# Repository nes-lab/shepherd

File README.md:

# SHEpHERD: SyncHronized Energy Harvesting Emulator RecorDer

**Testbed-Website**: <https://nes-lab.github.io/shepherd-nova>

**Python-Tools for Users**: <https://github.com/nes-lab/shepherd-tools>

**Documentation**: <https://nes-lab.github.io/shepherd>

**Main Project**: <https://github.com/nes-lab/shepherd>

**Targets-HW & -SW**: <https://github.com/nes-lab/shepherd-targets>

**WebAPI-Repo**: <https://github.com/nes-lab/shepherd-webapi>

**Dev-Documentation**: <https://github.com/orgua/shepherd-v2-planning>

---

Batteryless sensor nodes depend on harvesting energy from their environment.
Developing solutions involving groups of batteryless nodes requires a tool to analyze, understand and replicate spatio-temporal harvesting conditions.
*shepherd* is a testbed for the batteryless Internet of Things, allowing to record harvesting conditions at multiple points in space over time.
The recorded data can be replayed to attached wireless sensor nodes, examining their behavior under the constraints of spatio-temporal energy availability.

**Features**

- High-speed, high resolution current and voltage sensing
- Technology-agnostic: Currently, solar and kinetic energy harvesting are supported
- Remote programming/debugging of ARM Cortex-M MCUs using Serial-Wire-Debug
- High resolution, synchronized GPIO tracing
- Configurable, constant voltage power supply for attached sensor nodes
- Level-translated serial connection to the attached sensor nodes

For a detailed description see our [Paper](https://wwwpub.zih.tu-dresden.de/~mzimmerl/pubs/geissdoerfer19shepherd.pdf) or the [official documentation](https://nes-lab.github.io/shepherd/).

A *shepherd* instance consists of a group of spatially distributed *shepherd* nodes that are time-synchronized with each other.
Each *shepherd* node consists of a [BeagleBone](https://beagleboard.org/bone), the *shepherd* cape and either an energy harvesting source or a target MCU board to test.

This repository contains the hardware design files for the shepherd cape, the software running on each *shepherd* node as well as the tool to orchestrate a group of *shepherd* nodes connected to a network.

## Quickstart

Start by assembling your *shepherd* nodes, consisting of a BeagleBone Green/Black, a *shepherd* cape, a harvesting capelet and a target capelet.
The next step is to manually install the latest Ubuntu Linux on each BeagleBone.
You can install it to SD-card or the on-board eMMC flash, following [the official instructions](https://elinux.org/BeagleBoardUbuntu).
Make sure to follow the instructions for **BeagleBone**. Alternatively there are two more detailed guides in the [shepherd documentation](https://nes-lab.github.io/shepherd/user/getting_started.html).

The following instructions describe how to install the *shepherd* software on a group of *shepherd* nodes connected to an Ethernet network.
We assume that your local machine is connected to the same network, that the nodes have internet access and that you know the IP address of each node.

If you haven't done it yet, clone this repository to your local machine:

```shell
git clone https://github.com/nes-lab/shepherd.git
```

Next, install the tools used for installing and controlling the *shepherd* nodes.
We'll use [Ansible](https://www.ansible.com/) to remotely roll out the basic configuration to each *shepherd* node and *shepherd-herd* to orchestrate recording/emulation across all nodes.
The tools are hosted on `PyPI` and require Python version >= 3.6.
You'll also need to have `sshpass` installed on your machine, which is available through the package management system of all major distributions.
Install the tools using `pip`:

```shell
pip3 install ansible shepherd-herd
```

The `inventory/herd.yaml` file shows an example of how to provide the host names and known IP addresses of your BeagleBones.
Adjust it to reflect your setup.
You can arbitrarily choose and assign the hostnames (sheep0, sheep1, in this example) and the ansible_user (jane in this example).
[**TODO:** update description with roles].

```yaml
sheep:
  hosts:
    sheep0:
        ansible_host: 192.168.1.100
    sheep1:
        ansible_host: 192.168.1.101
    sheep2:
        ansible_host: 192.168.1.102
  vars:
    ansible_user: jane
```

Now run the `bootstrap.yml` *Ansible* playbook, which sets the hostname, creates a user and enables passwordless ssh and sudo:

```shell
ansible-playbook deploy/bootstrap.yml
```

Finally, use the `deploy.yml` playbook to set up the *shepherd* software with the configured roles from inventory:

```shell
ansible-playbook deploy/deploy.yml
```

## Usage

Record two minutes of data:

```shell
shepherd-herd harvester -d 120 -o recording.h5 -a mppt_voc
```

The command starts the recording asynchronously and returns after all nodes have started recording.
While the nodes are still recording (indicated by blinking of LED 1 and 2), prepare a directory on your local machine:

```shell
mkdir ~/shepherd_recordings
```

After the nodes stop blinking, you can retrieve the data to analyze it on your local machine:

```shell
shepherd-herd retrieve recording.h5 ~/shepherd_recordings
```

For a detailed description of the [HDF5](https://en.wikipedia.org/wiki/Hierarchical_Data_Format) based data format, refer to the [corresponding documentation](https://shepherd-testbed.readthedocs.io/en/latest/user/data_format.html).

Finally, replay the previously recorded data to the attached sensor nodes, recording their power consumption:

```shell
shepherd-herd emulator -o consumption.h5 recording.h5
```

Try `shepherd-herd --help` or check out the documentation [here](https://shepherd-testbed.readthedocs.io/en/latest/user/cli.html#shepherd-herd) for a list of all options.

## Problems and Questions

If you experience issues or require additional features, please get in touch via e-mail or by creating an issue on GitHub. The issue-tab also gives an overview for current roadmaps and milestones.

## People

*shepherd* development is lead at the Networked Embedded Systems Lab at TU Dresden & TU Darmstadt as part of the DFG-funded project Next-IoT.

The following people have contributed to *shepherd*:

- [Kai Geissdoerfer](https://www.researchgate.net/profile/Kai_Geissdoerfer)
- [Mikolaj Chwalisz](https://www.tkn.tu-berlin.de/team/chwalisz/)
- [Marco Zimmerling](https://wwwpub.zih.tu-dresden.de/~mzimmerl/)
- [Justus Paulick](https://github.com/kugelbit)
- [Boris Blokland](https://github.com/borro0)
- [Jonas Kubicki](https://github.com/jonkub)
- [Ingmar Splitt](https://github.com/nes-lab)

## Release-Procedure

Once you have a clean, stable and tested version, you should bump the version number to current year, month and release-number (YYYY.MM.r).

- increase version number by executing ``bump2version`` (see cmds below)
- update changelog in ``CHANGELOG.md``
- run unittests locally
  - sheep-package on observers
  - herd-tool on host
  - pru-python-module (in `software/firmware/pru0-module-py`)
  - fresh installation on Linux image via ansible
  - additionally every push gets automatically tested by GitHub workflows
- install and run ``prek`` for QA-Checks (pre-commit plugin-replacement), see steps below
- move code from dev-branch to main by PR
- add tag to commit - reflecting current version number - i.e. ``v25.5.1``
  - GitHub automatically creates a release & pushes the release to PyPI
- update release-text with latest Changelog (from `CHANGELOG.md`)
- rebase dev-branch

```Shell
prek run --all-files

# additional QA-Tests (currently with open issues)
ty check

bump2version --allow-dirty --new-version 2026.11.1 patch
# version-format: YYYY.MM.r
```

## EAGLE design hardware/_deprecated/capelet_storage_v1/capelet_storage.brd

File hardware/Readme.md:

# Shepherd specific Hardware

## Overview

Hardware-Subdirectories contain the necessary design-files to manufacture a shepherd observer node.

- `_deprecated`: design files for hardware that still floats around in the lab
- `cape_v#.#`: most recent version of shepherd cape for the BBone
- `case_lasercut`: deployment version for testbed
- ~~`power_in`:~~ low noise voltage regulator with < 17 V Input for TP-Link POE-Adapters that fail to produce 5V on newer Cisco Switches
- Targets are in dedicated [targets-repo](https://github.com/nes-lab/shepherd-targets/tree/main/hardware)

## Photos

### Cape v2.4

More pictures are stored for QA in [planning-repo](https://github.com/orgua/shepherd-v2-planning/tree/main/doc_testbed/photos_PCBs).

### Cape v2.5

No pictures available yet. Hardware is currently tested and then deployed.

### Observers

Assembled in October 2024 for the deployment at TU Dresden. These nodes contain:

- TP-Link POE Splitter
- BeagleBone Green
- Shepherd Cape v2.4
- [nRF FRAM Target v1.3](https://github.com/nes-lab/shepherd-targets/tree/main/hardware/shepherd_nRF_FRAM_Target_v1.3e)
- Power-in-PCB
- Laser-cut case

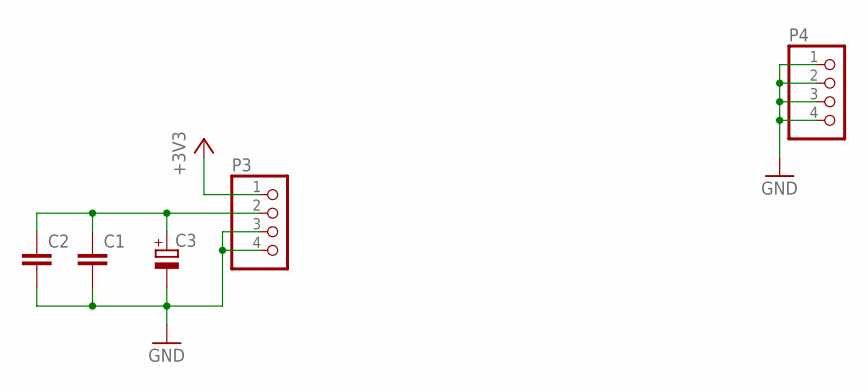
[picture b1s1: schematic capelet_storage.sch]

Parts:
C1: C_SMD0805; CAPC2012X145
C2: C_SMD1210; CAPC3225X280
C3: CPOL-EUE5-8.5; E5-8,5
P3, P4: PINHD-1X4; 1X04

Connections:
+3V3: P3.1
GND: C1.2, C2.2, C3.-, P3.3, P3.4, P4.1, P4.2, P4.3, P4.4
unnamed: C1.1, C2.1, C3.+, P3.2

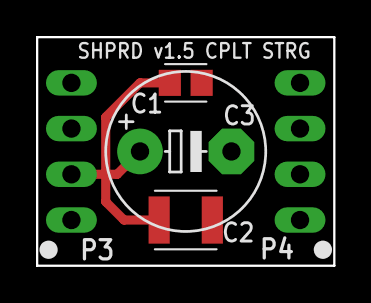
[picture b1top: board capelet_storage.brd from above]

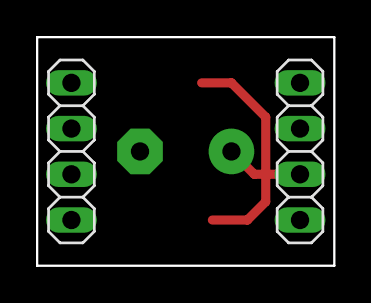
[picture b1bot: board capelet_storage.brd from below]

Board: 2 copper layers, 16.5 x 12.7 mm, 6 parts (2 on the bottom side), 2 nets.

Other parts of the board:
U$1: SHPRD_CPLT_S

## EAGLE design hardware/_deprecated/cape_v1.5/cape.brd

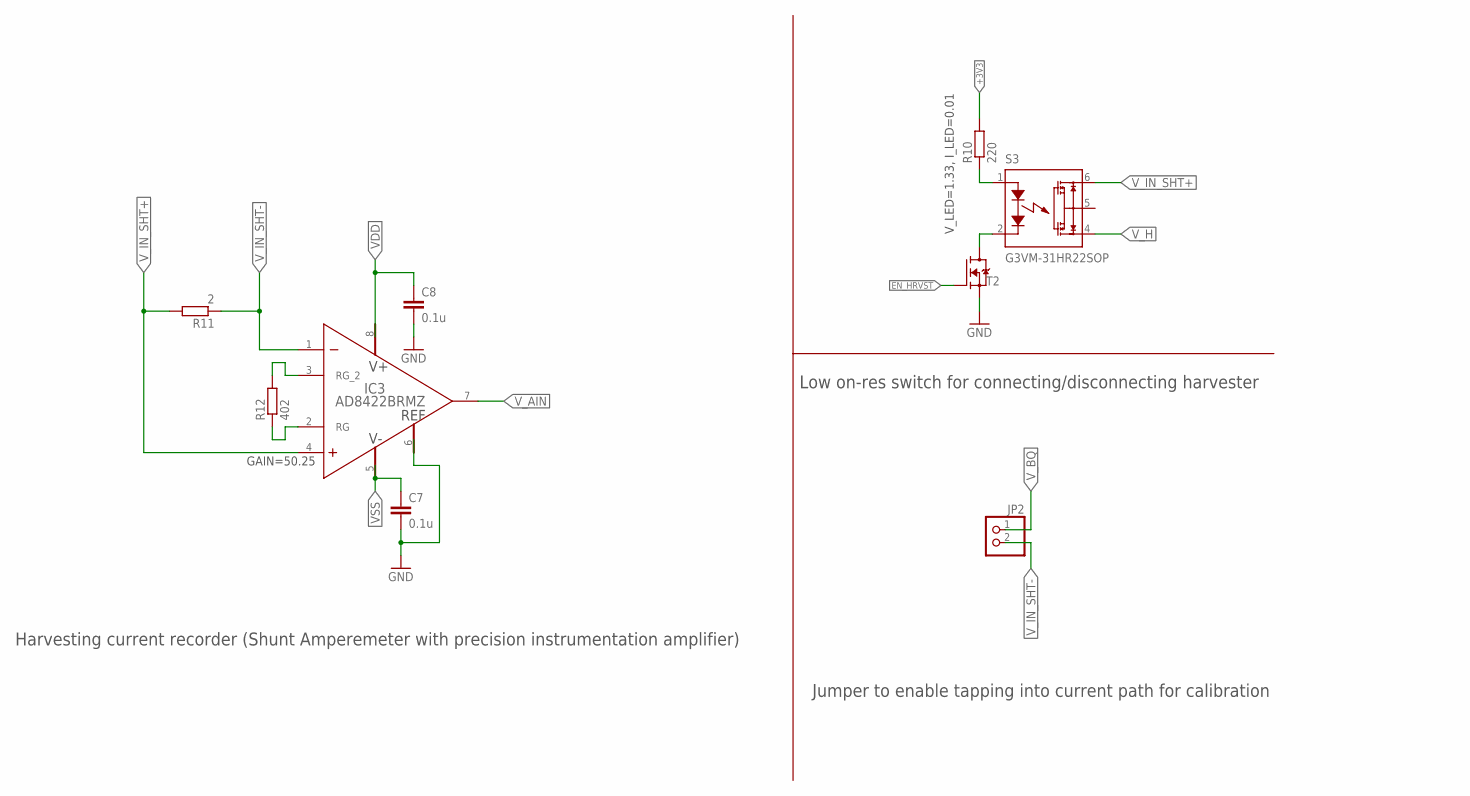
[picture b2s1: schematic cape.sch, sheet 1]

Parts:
C7, C8: 0.1u; CAPC1005X55
IC3: AD8422BRMZ; RM_8-L
JP2: PINHD-1X2; 1X02
R10: 220; RESC1608X55
R11: 2; RESC1608X55
R12: 402; RESC1608X55
S3: G3VM-31HR22SOP; SOP06
T2: SI2374DSSOT23-VSHAY; SOT95P237X112-3

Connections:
+3V3: R10.2; also elsewhere on the board
EN_HRVST: T2.1 (G); also elsewhere on the board
GND: C7.2, C8.2, IC3.6 (REF), T2.2 (S); also elsewhere on the board
unnamed: R10.1, S3.1 (A)
unnamed: IC3.3 (RG_2), R12.2
unnamed: IC3.2 (RG), R12.1
unnamed: S3.2 (K), T2.3 (D)
VDD: C8.1, IC3.8 (V+); also elsewhere on the board
VSS: C7.1, IC3.5 (V-); also elsewhere on the board
V_AIN: IC3.7 (OUT); also elsewhere on the board
V_BQ: JP2.1; also elsewhere on the board
V_H: S3.4 (D2); also elsewhere on the board
V_IN_SHT+: IC3.4 (IN+), R11.2, S3.6 (D1); also elsewhere on the board
V_IN_SHT-: IC3.1 (IN-), JP2.2, R11.1; also elsewhere on the board

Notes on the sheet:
V_LED=1.33, I_LED=0.01
GAIN=50.25
Harvesting current recorder (Shunt Amperemeter with precision instrumentation amplifier)
Low on-res switch for connecting/disconnecting harvester
Jumper to enable tapping into current path for calibration

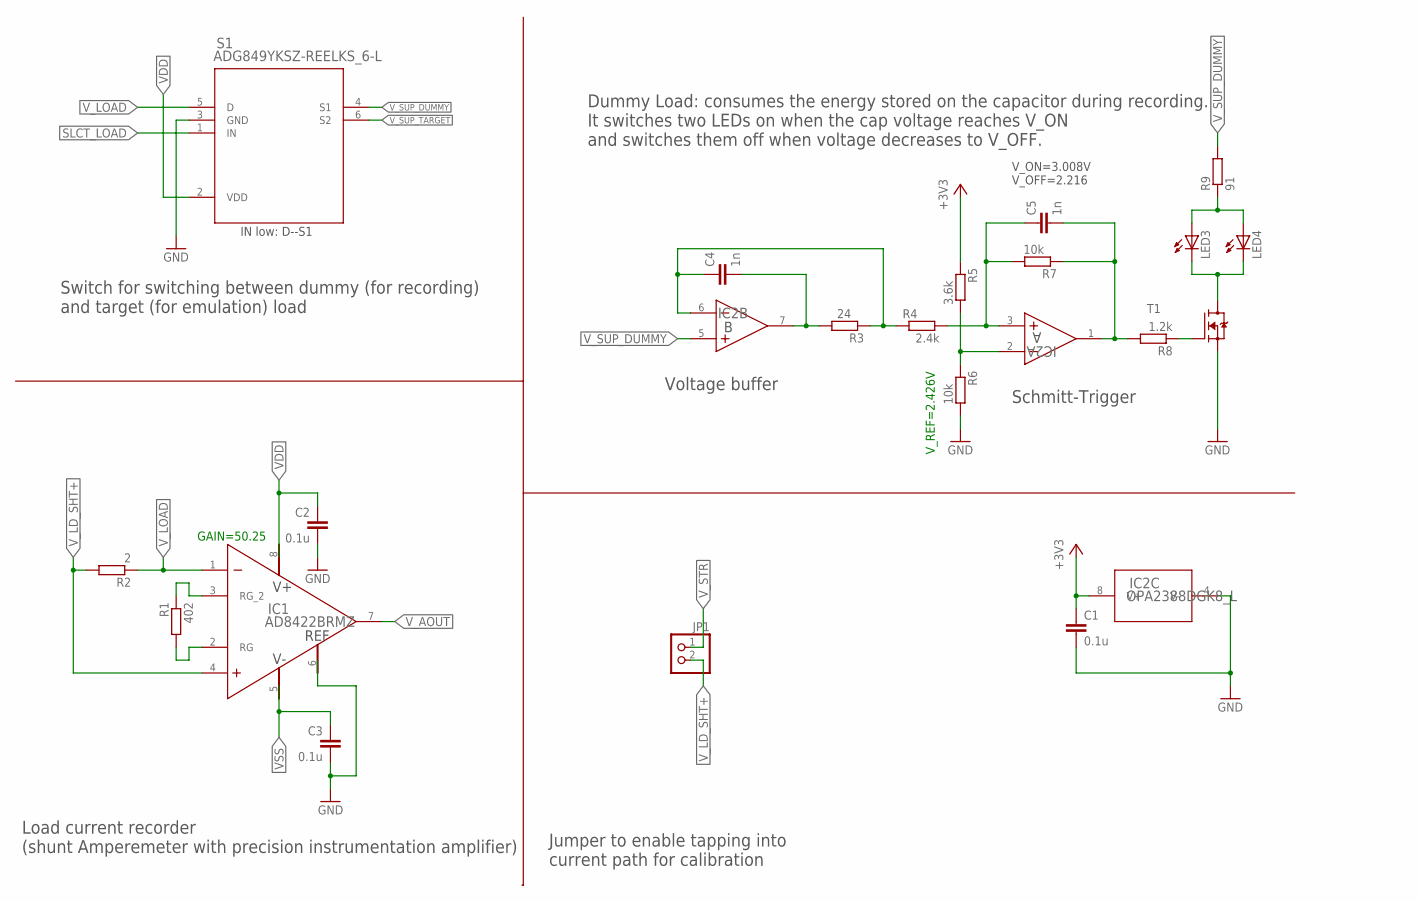
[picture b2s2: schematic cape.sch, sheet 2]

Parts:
C1, C2, C3: 0.1u; CAPC1005X55
C4, C5: 1n; CAPC1005X55
IC1: AD8422BRMZ; RM_8-L
IC2: OPA2388DGK8_L; DGK8-L
JP1: PINHD-1X2; 1X02
LED3, LED4: 598-8130-107FLED_0805; LEDC2012X75
R1: 402; RESC1608X55
R2: 2; RESC1608X55
R3: 24; RESC1005X40
R4: 2.4k; RESC1005X40
R5: 3.6k; RESC1005X40
R6, R7: 10k; RESC1005X40
R8: 1.2k; RESC1005X40
R9: 91; RESC1608X55
S1: ADG849YKSZ-REELKS_6-L; KS_6-L
T1: SI2374DSSOT23-VSHAY; SOT95P237X112-3

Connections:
+3V3: C1.1, IC2.8 (V+), R5.1; also elsewhere on the board
GND: C1.2, C2.2, C3.2, IC1.6 (REF), IC2.4 (V-), R6.2, S1.3 (GND), T1.2 (S); also elsewhere on the board
unnamed: R8.1, T1.1 (G)
unnamed: LED3.2 (A), LED4.2 (A), R9.1
unnamed: C5.2, IC2.1 (OUT), R7.1, R8.2
unnamed: LED3.1 (C), LED4.1 (C), T1.3 (D)
unnamed: C5.1, IC2.3 (IN+), R4.2, R7.2
unnamed: IC2.2 (IN-), R5.2, R6.1
unnamed: C4.1, IC2.6 (IN-), R3.1, R4.1
unnamed: C4.2, IC2.7 (OUT), R3.2
unnamed: IC1.2 (RG), R1.2
unnamed: IC1.3 (RG_2), R1.1
SLCT_LOAD: S1.1 (IN); also elsewhere on the board
VDD: C2.1, IC1.8 (V+), S1.2 (VDD); also elsewhere on the board
VSS: C3.1, IC1.5 (V-); also elsewhere on the board
V_AOUT: IC1.7 (OUT); also elsewhere on the board
V_LD_SHT+: IC1.4 (IN+), JP1.2, R2.2; also elsewhere on the board
V_LOAD: IC1.1 (IN-), R2.1, S1.5 (D); also elsewhere on the board
V_STR: JP1.1; also elsewhere on the board
V_SUP_DUMMY: IC2.5 (IN+), R9.2, S1.4 (S1)
V_SUP_TARGET: S1.6 (S2); also elsewhere on the board

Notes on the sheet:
IN low: D--S1
GAIN=50.25
V_REF=2.426V
V_ON=3.008V V_OFF=2.216
Dummy Load: consumes the energy stored on the capacitor during recording. It switches two LEDs on when the cap voltage reaches V_ON and switches them off when voltage decreases to V_OFF.
Voltage buffer
Schmitt-Trigger
Switch for switching between dummy (for recording) and target (for emulation) load
Load current recorder (shunt Amperemeter with precision instrumentation amplifier)
Jumper to enable tapping into current path for calibration

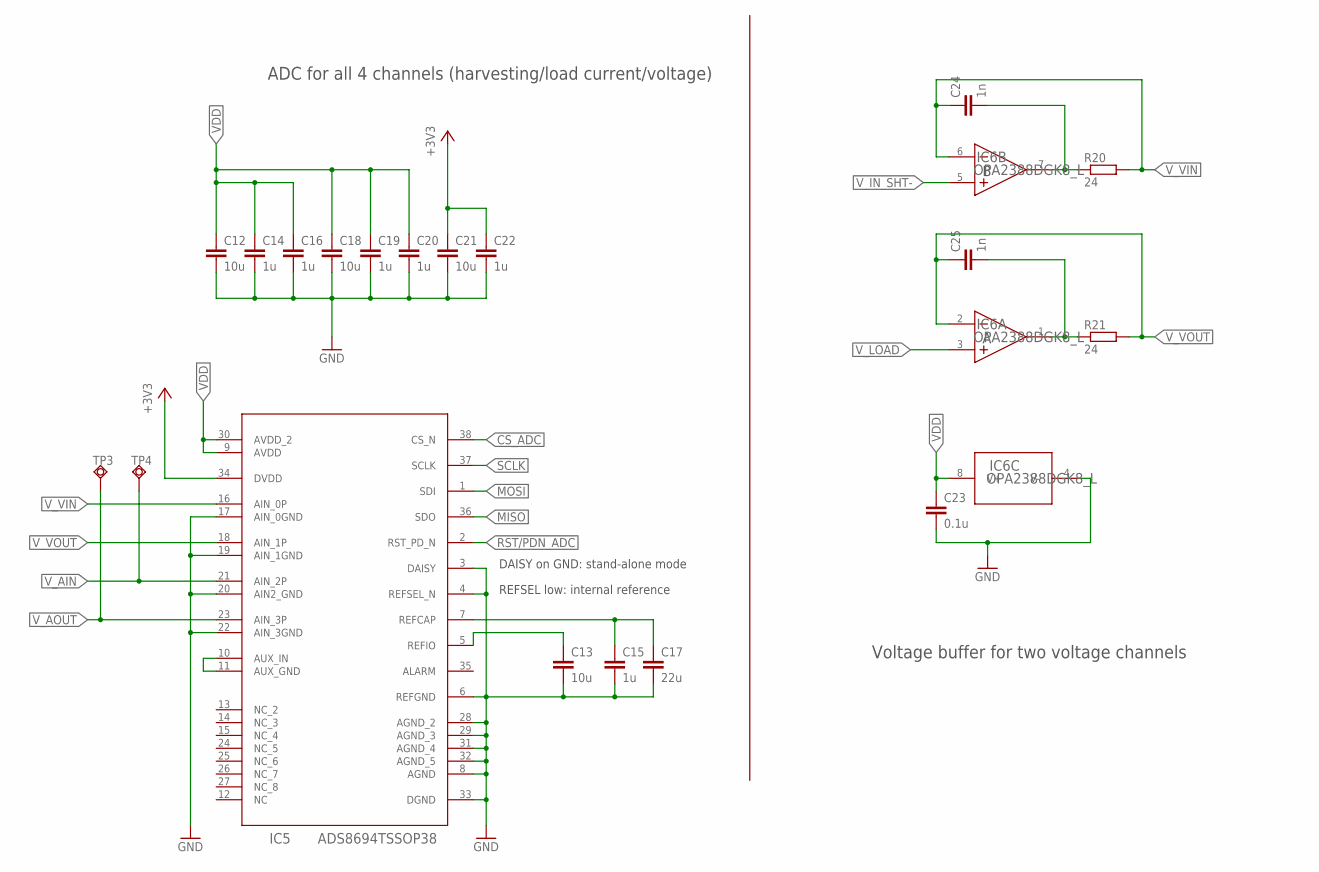
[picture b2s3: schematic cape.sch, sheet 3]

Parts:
C12, C13, C18, C21: 10u; CAPC2012X145
C14, C15, C16, C19, C20, C22: 1u; CAPC1608X95
C17: 22u; CAPC3225X280
C23: 0.1u; CAPC1005X55
C24, C25: 1n; CAPC1005X55
IC5: ADS8694TSSOP38; TSSOP38
IC6: OPA2388DGK8_L; DGK8-L
R20, R21: 24; RESC1005X40
TP3, TP4: TPSQTP06R; TP06R

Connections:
+3V3: C21.1, C22.1, IC5.34 (DVDD); also elsewhere on the board
CS_ADC: IC5.38 (CS_N); also elsewhere on the board
GND: C12.2, C13.2, C14.2, C15.2, C16.2, C17.2, C18.2, C19.2, C20.2, C21.2, C22.2, C23.2, IC5.3 (DAISY), IC5.4 (REFSEL_N), IC5.6 (REFGND), IC5.8 (AGND), IC5.17 (AIN_0GND), IC5.19 (AIN_1GND), IC5.20 (AIN2_GND), IC5.22 (AIN_3GND), IC5.28 (AGND_2), IC5.29 (AGND_3), IC5.31 (AGND_4), IC5.32 (AGND_5), IC5.33 (DGND), IC6.4 (V-); also elsewhere on the board
MISO: IC5.36 (SDO); also elsewhere on the board
MOSI: IC5.1 (SDI); also elsewhere on the board
unnamed: C13.1, IC5.5 (REFIO)
unnamed: C15.1, C17.1, IC5.7 (REFCAP)
unnamed: IC5.10 (AUX_IN), IC5.11 (AUX_GND)
unnamed: C25.2, IC6.1 (OUT), R21.1
unnamed: C24.2, IC6.7 (OUT), R20.1
RST/PDN_ADC: IC5.2 (RST_PD_N); also elsewhere on the board
SCLK: IC5.37 (SCLK); also elsewhere on the board
VDD: C12.1, C14.1, C16.1, C18.1, C19.1, C20.1, C23.1, IC5.9 (AVDD), IC5.30 (AVDD_2), IC6.8 (V+); also elsewhere on the board
V_AIN: IC5.21 (AIN_2P), TP4.TP; also elsewhere on the board
V_AOUT: IC5.23 (AIN_3P), TP3.TP; also elsewhere on the board
V_IN_SHT-: IC6.5 (IN+); also elsewhere on the board
V_LOAD: IC6.3 (IN+); also elsewhere on the board
V_VIN: C24.1, IC5.16 (AIN_0P), IC6.6 (IN-), R20.2
V_VOUT: C25.1, IC5.18 (AIN_1P), IC6.2 (IN-), R21.2

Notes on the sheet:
REFSEL low: internal reference
DAISY on GND: stand-alone mode
ADC for all 4 channels (harvesting/load current/voltage)
Voltage buffer for two voltage channels

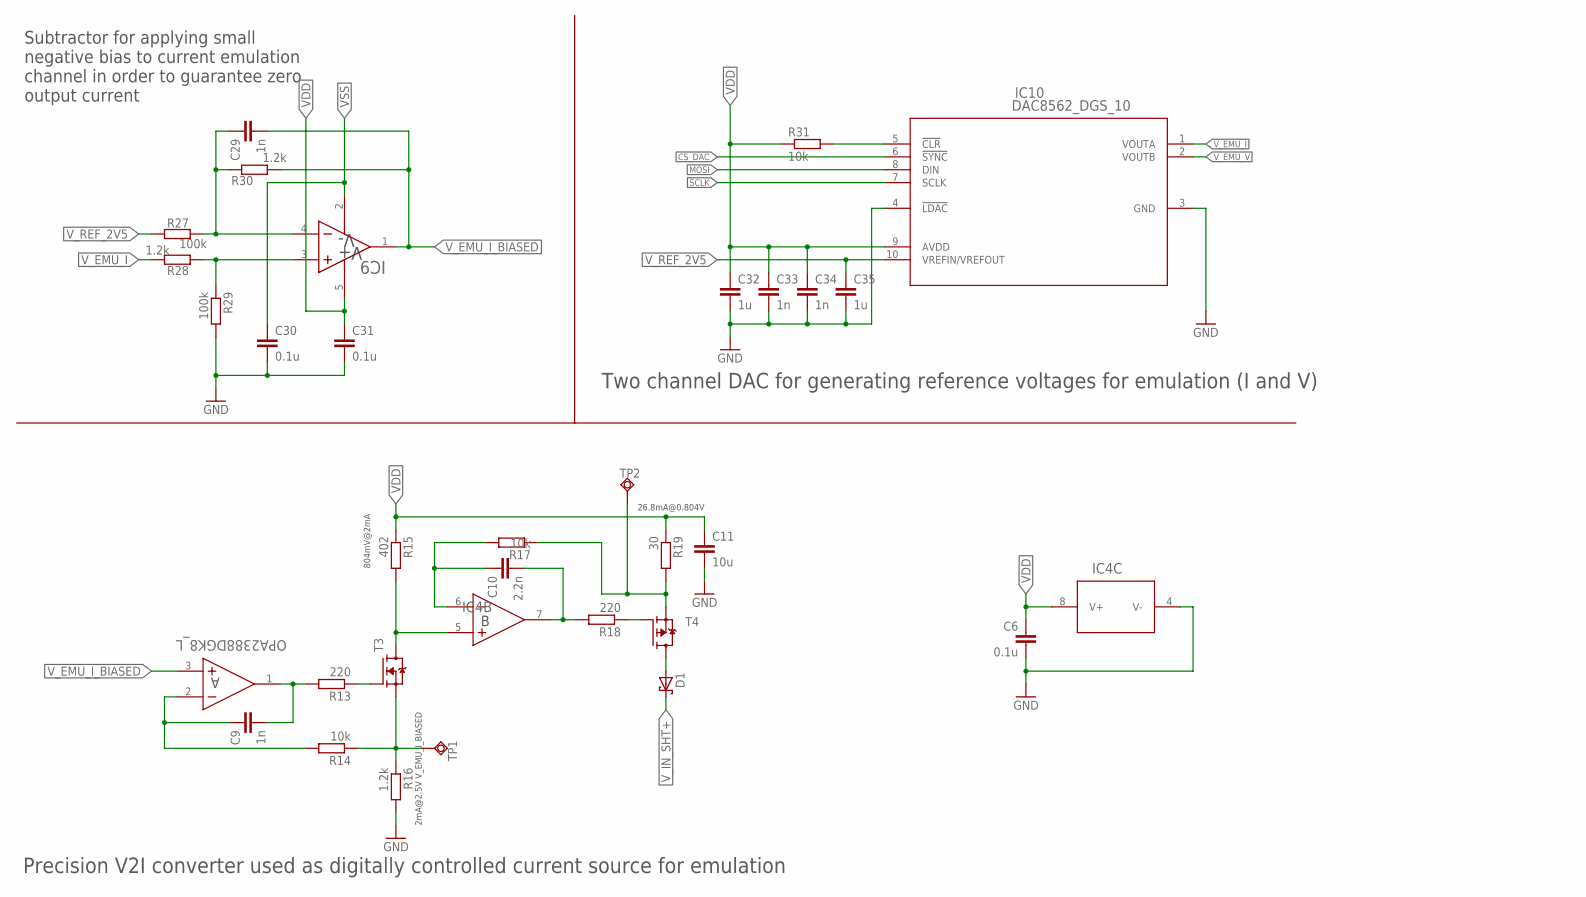
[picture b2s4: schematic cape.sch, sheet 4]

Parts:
C6, C30, C31: 0.1u; CAPC1005X55
C9, C29, C33, C34: 1n; CAPC1005X55
C10: 2.2n; CAPC1005X55
C11: 10u; CAPC2012X145
C32, C35: 1u; CAPC1608X95
D1: BAT43WS-HE3SOD-323; SOD2513X110
IC4: OPA2388DGK8_L; DGK8-L
IC9: LMP7701MF; DBV5-L
IC10: DAC8562_DGS_10; DGS10
R13, R18: 220; RESC1608X55
R14, R17, R31: 10k; RESC1005X40
R15: 402; RESC1608X55
R16, R28, R30: 1.2k; RESC1005X40
R19: 30; RESC1005X40
R27, R29: 100k; RESC1005X40
T3: SI2374DSSOT23-VSHAY; SOT95P237X112-3
T4: SI2307SOT23-VSHAY; SOT95P237X112-3
TP1, TP2: TPSQTP06R; TP06R

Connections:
CS_DAC: IC10.6 (!SYNC); also elsewhere on the board
GND: C6.2, C11.2, C30.2, C31.2, C32.2, C33.2, C34.2, C35.2, IC4.4 (V-), IC10.3 (GND), IC10.4 (!LDAC), R16.2, R29.2; also elsewhere on the board
MOSI: IC10.8 (DIN); also elsewhere on the board
unnamed: C9.2, IC4.1 (OUT), R13.2
unnamed: C9.1, IC4.2 (IN-), R14.2
unnamed: IC10.5 (!CLR), R31.2
unnamed: D1.2 (A), T4.3 (D)
unnamed: C29.1, IC9.4 (IN-), R27.1, R30.2
unnamed: IC9.3 (IN+), R28.1, R29.1
unnamed: R13.1, T3.1 (G)
unnamed: R14.1, R16.1, T3.2 (S), TP1.TP
unnamed: IC4.5 (IN+), R15.2, T3.3 (D)
unnamed: C10.1, IC4.6 (IN-), R17.2
unnamed: C10.2, IC4.7 (OUT), R18.2
unnamed: R18.1, T4.1 (G)
unnamed: R17.1, R19.2, T4.2 (S), TP2.TP
SCLK: IC10.7 (SCLK); also elsewhere on the board
VDD: C6.1, C11.1, C31.1, C32.1, C33.1, C34.1, IC4.8 (V+), IC9.5 (V+), IC10.9 (AVDD), R15.1, R19.1, R31.1; also elsewhere on the board
VSS: C30.1, IC9.2 (V-); also elsewhere on the board
V_EMU_I: IC10.1 (VOUTA), R28.2
V_EMU_I_BIASED: C29.2, IC4.3 (IN+), IC9.1 (OUT), R30.1
V_EMU_V: IC10.2 (VOUTB); also elsewhere on the board
V_IN_SHT+: D1.1 (C); also elsewhere on the board
V_REF_2V5: C35.1, IC10.10 (VREFIN/VREFOUT), R27.2

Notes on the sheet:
Two channel DAC for generating reference voltages for emulation (I and V)
Subtractor for applying small negative bias to current emulation channel in order to guarantee zero output current
2mA@2.5V V_EMU_I_BIASED
804mV@2mA
26.8mA@0.804V
Precision V2I converter used as digitally controlled current source for emulation

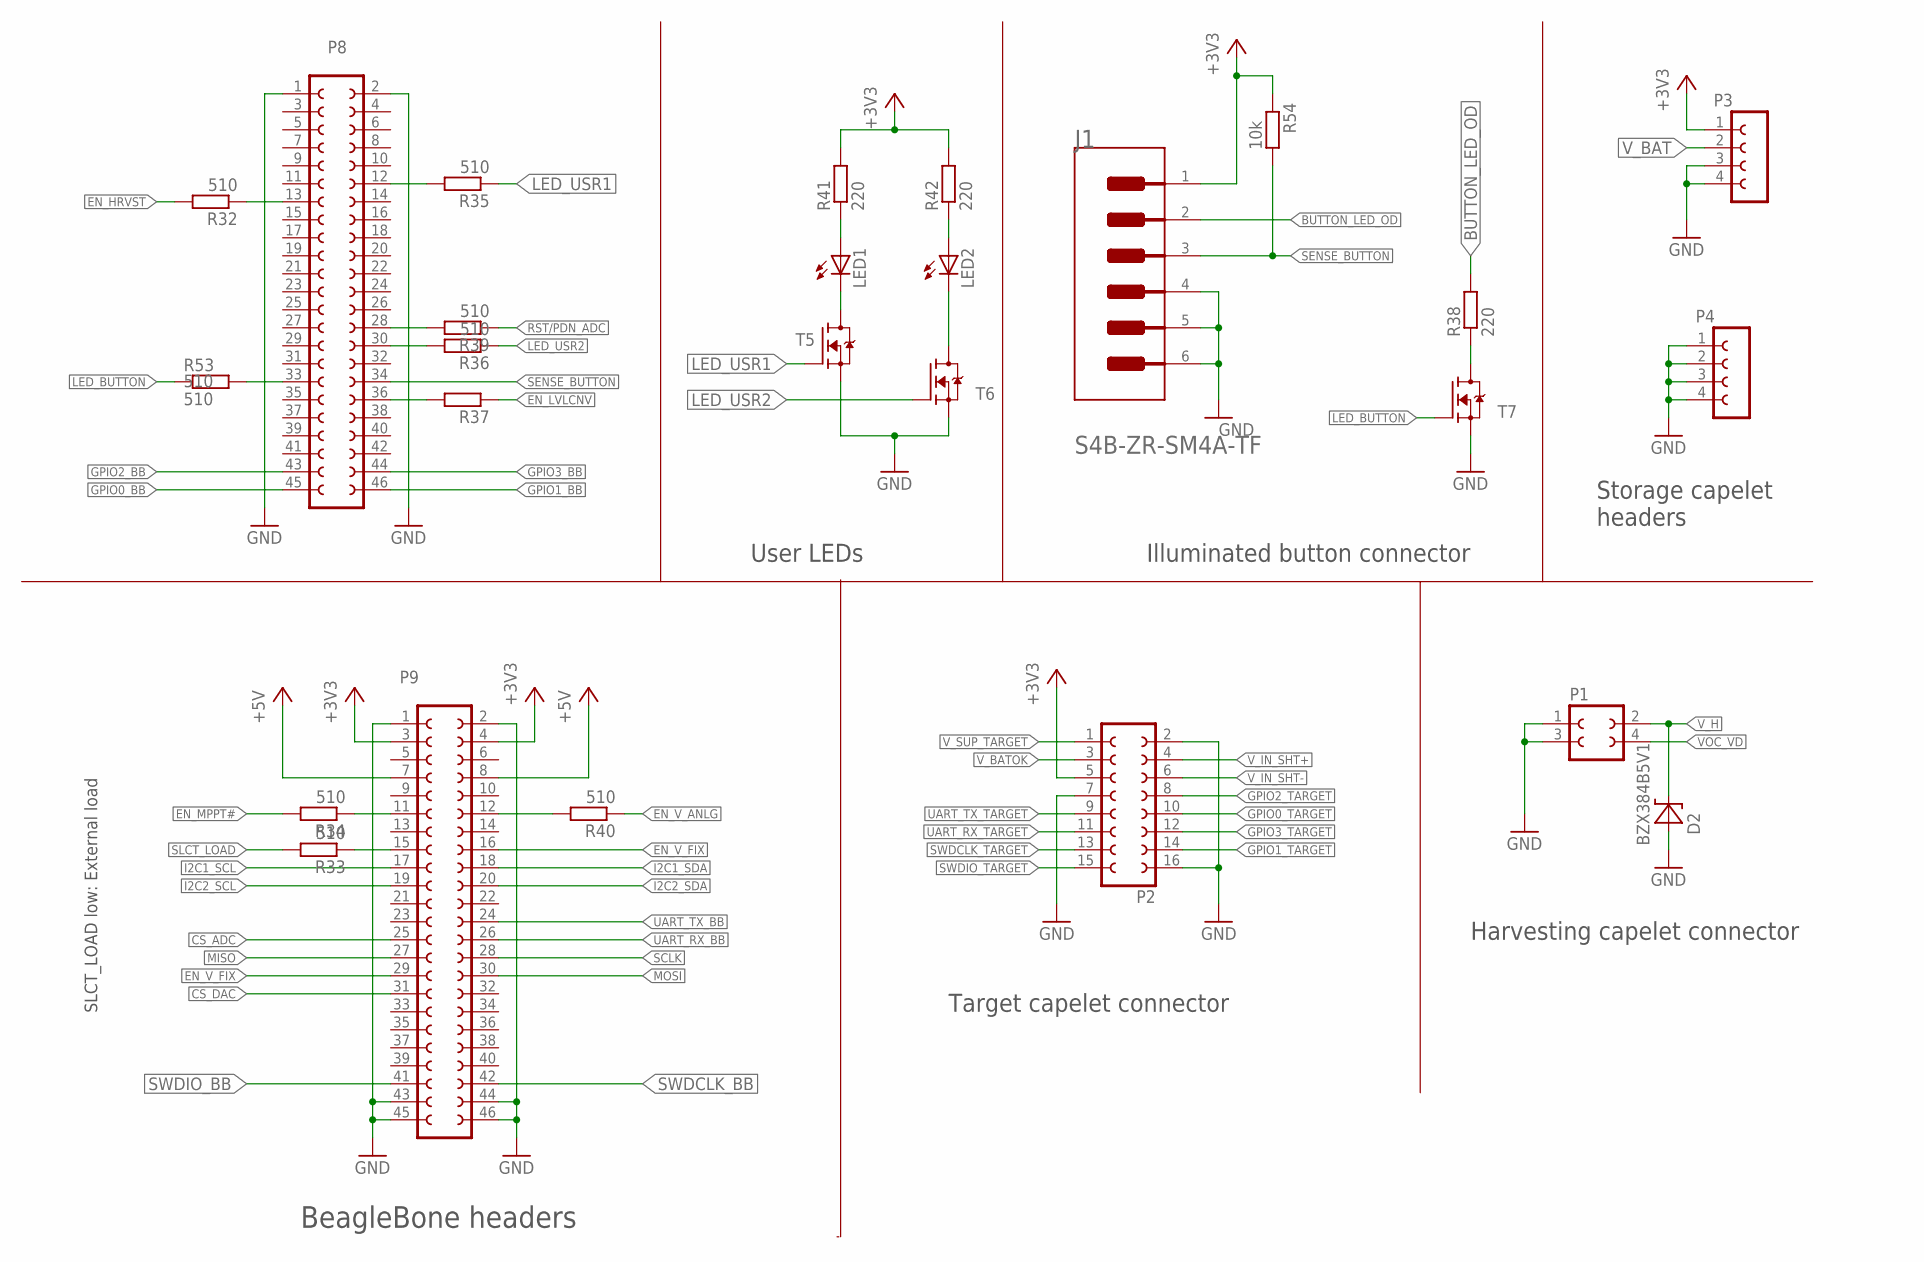
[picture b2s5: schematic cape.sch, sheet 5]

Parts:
D2: BZX384B5V1; SOD2513X110
J1: JST_S4B-ZR-SM4A-TFJST_S4B-ZR-SM4A-TF_0_0; JST_S4B-ZR-SM4A-TF_0
LED1, LED2: 598-8130-107FLED_0805; LEDC2012X75
P1: FE02-2
P2: FE08-2
P3, P4: FE04-1
P8, P9: FE23-2
R32, R33, R34, R35, R36, R37, R39, R40, R53: 510; RESC1005X40
R38, R41, R42: 220; RESC1608X55
R54: 10k; RESC1005X40
T5, T6, T7: SI2374DSSOT23-VSHAY; SOT95P237X112-3

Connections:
+3V3: J1.1, P2.5, P3.1, P9.3, P9.4, R41.2, R42.2, R54.1; also elsewhere on the board
+5V: P9.7, P9.8; also elsewhere on the board
BUTTON_LED_OD: J1.2, R38.2
CS_ADC: P9.25; also elsewhere on the board
CS_DAC: P9.31; also elsewhere on the board
EN_HRVST: R32.2; also elsewhere on the board
EN_LVLCNV: R37.1; also elsewhere on the board
EN_MPPT#: R34.2; also elsewhere on the board
EN_V_ANLG: R40.1; also elsewhere on the board
EN_V_FIX: P9.16, P9.29; also elsewhere on the board
GND: D2.2 (A), J1.4, J1.5 (MNT_1), J1.6 (MNT_2), P1.1, P1.3, P2.2, P2.7, P2.16, P3.3, P3.4, P4.1, P4.2, P4.3, P4.4, P8.1, P8.2, P9.1, P9.2, P9.43, P9.44, P9.45, P9.46, T5.2 (S), T6.2 (S), T7.2 (S); also elsewhere on the board
GPIO0_BB: P8.45; also elsewhere on the board
GPIO0_TARGET: P2.10; also elsewhere on the board
GPIO1_BB: P8.46; also elsewhere on the board
GPIO1_TARGET: P2.14; also elsewhere on the board
GPIO2_BB: P8.43; also elsewhere on the board
GPIO2_TARGET: P2.8; also elsewhere on the board
GPIO3_BB: P8.44; also elsewhere on the board
GPIO3_TARGET: P2.12; also elsewhere on the board
I2C1_SCL: P9.17; also elsewhere on the board
I2C1_SDA: P9.18; also elsewhere on the board
I2C2_SCL: P9.19; also elsewhere on the board
I2C2_SDA: P9.20; also elsewhere on the board
LED_BUTTON: R53.1, T7.1 (G)
LED_USR1: R35.1, T5.1 (G)
LED_USR2: R36.1, T6.1 (G)
MISO: P9.27; also elsewhere on the board
MOSI: P9.30; also elsewhere on the board
unnamed: LED1.1 (C), T5.3 (D)
unnamed: P8.13, R32.1
unnamed: P9.15, R33.1
unnamed: P8.28, R39.2
unnamed: P8.33, R53.2
unnamed: P8.36, R37.2
unnamed: LED1.2 (A), R41.1
unnamed: P8.12, R35.2
unnamed: LED2.1 (C), T6.3 (D)
unnamed: LED2.2 (A), R42.1
unnamed: P9.11, R34.1
unnamed: P8.30, R36.2
unnamed: R38.1, T7.3 (D)
unnamed: P9.12, R40.2
RST/PDN_ADC: R39.1; also elsewhere on the board
SCLK: P9.28; also elsewhere on the board
SENSE_BUTTON: J1.3, P8.34, R54.2
SLCT_LOAD: R33.2; also elsewhere on the board
SWDCLK_BB: P9.42; also elsewhere on the board
SWDCLK_TARGET: P2.13; also elsewhere on the board
SWDIO_BB: P9.41; also elsewhere on the board
SWDIO_TARGET: P2.15; also elsewhere on the board
UART_RX_BB: P9.26; also elsewhere on the board
UART_RX_TARGET: P2.11; also elsewhere on the board
UART_TX_BB: P9.24; also elsewhere on the board
UART_TX_TARGET: P2.9; also elsewhere on the board
VOC_VD: P1.4; also elsewhere on the board
V_BAT: P3.2; also elsewhere on the board
V_BATOK: P2.3; also elsewhere on the board
V_H: D2.1 (C), P1.2; also elsewhere on the board
V_IN_SHT+: P2.4; also elsewhere on the board
V_IN_SHT-: P2.6; also elsewhere on the board
V_SUP_TARGET: P2.1; also elsewhere on the board

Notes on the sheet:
SLCT_LOAD low: External load
Storage capelet headers
User LEDs
Harvesting capelet connector
Target capelet connector
BeagleBone headers
Illuminated button connector

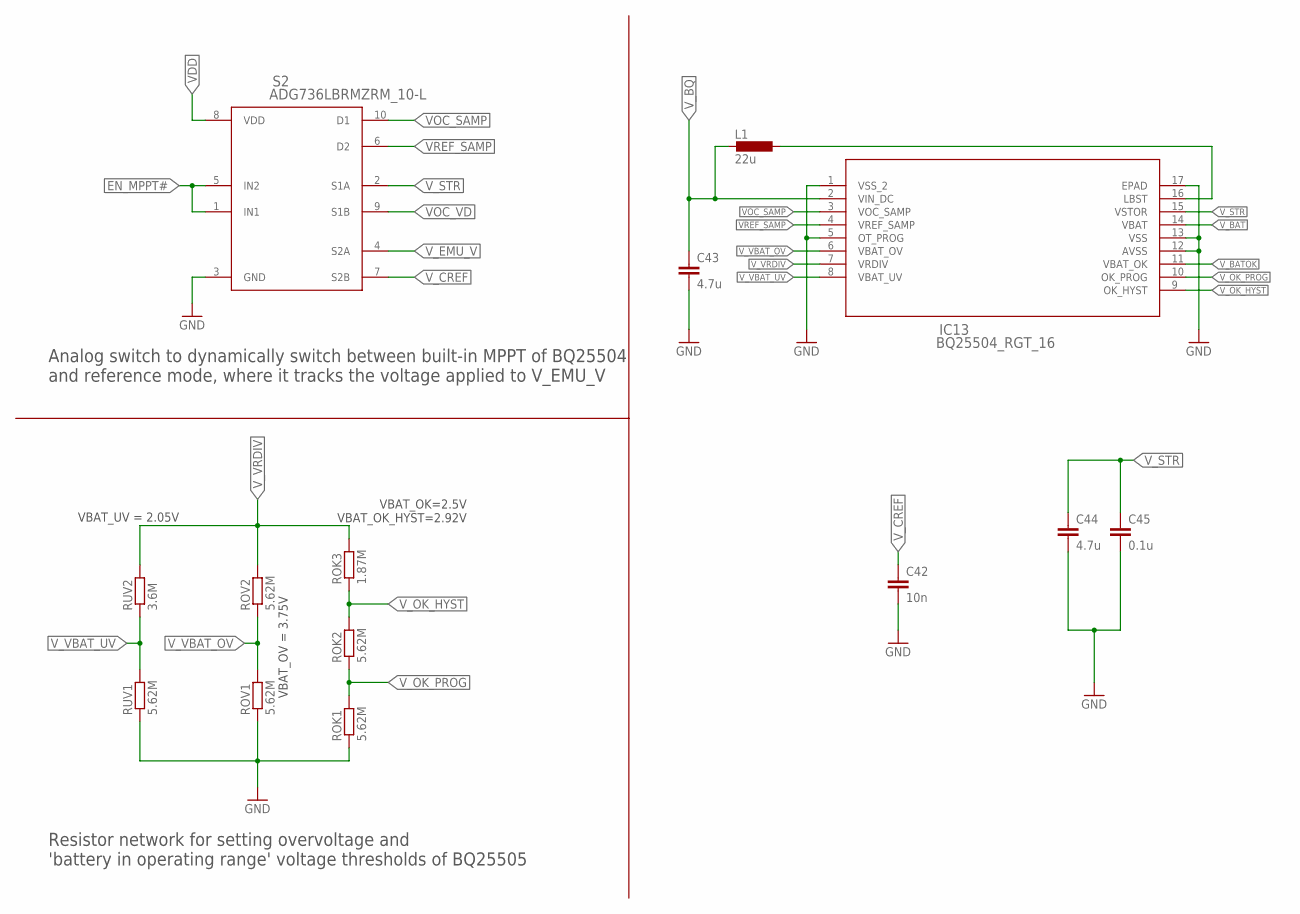
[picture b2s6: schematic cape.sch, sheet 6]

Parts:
C42: 10n; CAPC1005X55
C43, C44: 4.7u; CAPC2012X145
C45: 0.1u; CAPC1005X55
IC13: BQ25504_RGT_16; RGT16_1P7X1P7
L1: 22u; L3225P
ROK1, ROK2: 5.62M; RESC1608X55
ROK3: 1.87M; RESC1608X55
ROV1, ROV2: 5.62M; RESC1608X55
RUV1: 5.62M; RESC1608X55
RUV2: 3.6M; RESC1608X55
S2: ADG736LBRMZRM_10-L; RM_10-L

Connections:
EN_MPPT#: S2.1 (IN1), S2.5 (IN2); also elsewhere on the board
GND: C42.2, C43.2, C44.2, C45.2, IC13.1 (VSS_2), IC13.5 (OT_PROG), IC13.12 (AVSS), IC13.13 (VSS), IC13.17 (EPAD), ROK1.1, ROV1.1, RUV1.1, S2.3 (GND); also elsewhere on the board
unnamed: IC13.16 (LBST), L1.1
VDD: S2.8 (VDD); also elsewhere on the board
VOC_SAMP: IC13.3 (VOC_SAMP), S2.10 (D1)
VOC_VD: S2.9 (S1B); also elsewhere on the board
VREF_SAMP: IC13.4 (VREF_SAMP), S2.6 (D2)
V_BAT: IC13.14 (VBAT); also elsewhere on the board
V_BATOK: IC13.11 (VBAT_OK); also elsewhere on the board
V_BQ: C43.1, IC13.2 (VIN_DC), L1.2; also elsewhere on the board
V_CREF: C42.1, S2.7 (S2B)
V_EMU_V: S2.4 (S2A); also elsewhere on the board
V_OK_HYST: IC13.9 (OK_HYST), ROK2.2, ROK3.1
V_OK_PROG: IC13.10 (OK_PROG), ROK1.2, ROK2.1
V_STR: C44.1, C45.1, IC13.15 (VSTOR), S2.2 (S1A); also elsewhere on the board
V_VBAT_OV: IC13.6 (VBAT_OV), ROV1.2, ROV2.1
V_VBAT_UV: IC13.8 (VBAT_UV), RUV1.2, RUV2.1
V_VRDIV: IC13.7 (VRDIV), ROK3.2, ROV2.2, RUV2.2

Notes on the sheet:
VBAT_OK=2.5V VBAT_OK_HYST=2.92V
VBAT_OV = 3.75V
Analog switch to dynamically switch between built-in MPPT of BQ25504 and reference mode, where it tracks the voltage applied to V_EMU_V
Resistor network for setting overvoltage and 'battery in operating range' voltage thresholds of BQ25505
VBAT_UV = 2.05V

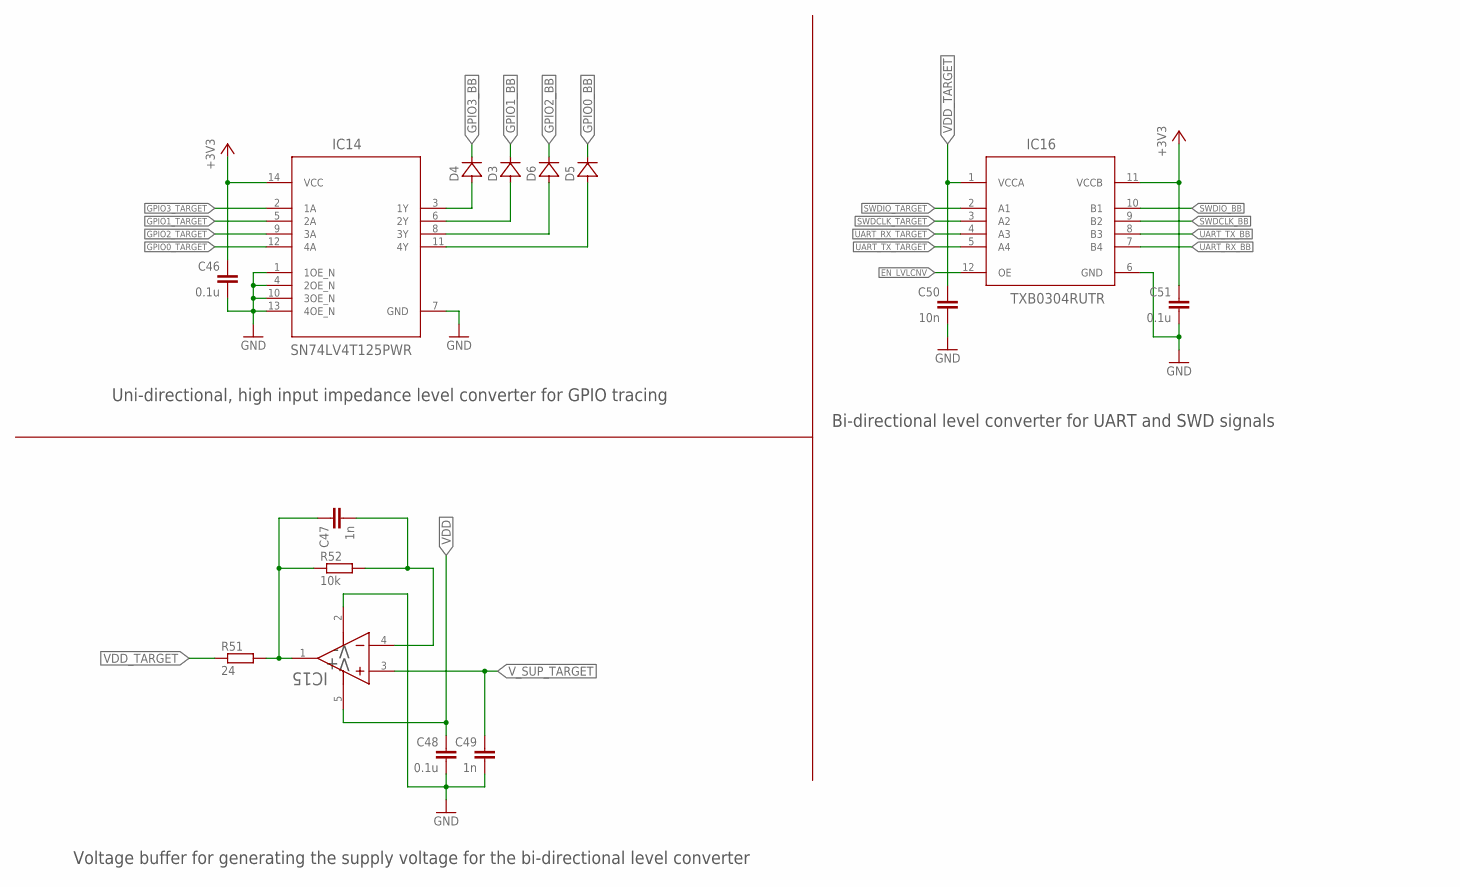
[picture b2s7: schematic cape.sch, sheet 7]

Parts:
C46, C48, C51: 0.1u; CAPC1005X55
C47, C49: 1n; CAPC1005X55
C50: 10n; CAPC1005X55
D3, D4, D5, D6: ACDBQC0130L-HF0402; DIOC1005X55N
IC14: SN74LV4T125PWR; PW0014A_N
IC15: LMP7701MF; DBV5-L
IC16: TXB0304RUTR; RUT0012A
R51: 24; RESC1005X40
R52: 10k; RESC1005X40

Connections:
+3V3: C46.1, C51.1, IC14.14 (VCC), IC16.11 (VCCB); also elsewhere on the board
EN_LVLCNV: IC16.12 (OE); also elsewhere on the board
GND: C46.2, C48.2, C49.2, C50.2, C51.2, IC14.1 (1OE_N), IC14.4 (2OE_N), IC14.7 (GND), IC14.10 (3OE_N), IC14.13 (4OE_N), IC15.2 (V-), IC16.6 (GND); also elsewhere on the board
GPIO0_BB: D5.2 (C); also elsewhere on the board
GPIO0_TARGET: IC14.12 (4A); also elsewhere on the board
GPIO1_BB: D3.2 (C); also elsewhere on the board
GPIO1_TARGET: IC14.5 (2A); also elsewhere on the board
GPIO2_BB: D6.2 (C); also elsewhere on the board
GPIO2_TARGET: IC14.9 (3A); also elsewhere on the board
GPIO3_BB: D4.2 (C); also elsewhere on the board
GPIO3_TARGET: IC14.2 (1A); also elsewhere on the board
unnamed: D4.1 (A), IC14.3 (1Y)
unnamed: C47.1, IC15.1 (OUT), R51.2, R52.1
unnamed: D3.1 (A), IC14.6 (2Y)
unnamed: D6.1 (A), IC14.8 (3Y)
unnamed: D5.1 (A), IC14.11 (4Y)
unnamed: C47.2, IC15.4 (IN-), R52.2
SWDCLK_BB: IC16.9 (B2); also elsewhere on the board
SWDCLK_TARGET: IC16.3 (A2); also elsewhere on the board
SWDIO_BB: IC16.10 (B1); also elsewhere on the board
SWDIO_TARGET: IC16.2 (A1); also elsewhere on the board
UART_RX_BB: IC16.7 (B4); also elsewhere on the board
UART_RX_TARGET: IC16.4 (A3); also elsewhere on the board
UART_TX_BB: IC16.8 (B3); also elsewhere on the board
UART_TX_TARGET: IC16.5 (A4); also elsewhere on the board
VDD: C48.1, IC15.5 (V+); also elsewhere on the board
VDD_TARGET: C50.1, IC16.1 (VCCA), R51.1
V_SUP_TARGET: C49.1, IC15.3 (IN+); also elsewhere on the board

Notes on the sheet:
Bi-directional level converter for UART and SWD signals
Uni-directional, high input impedance level converter for GPIO tracing
Voltage buffer for generating the supply voltage for the bi-directional level converter
